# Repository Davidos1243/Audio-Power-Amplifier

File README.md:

# High-Fidelity Audio Power Amplifier (Class AB)

## 📌 Project Overview
This project involves the complete design, simulation, and PCB layout of a **Class AB audio power amplifier** designed specifically for high-frequency speakers (tweeters). The system is built around the Texas Instruments **LM3886** power amplifier IC and features active filtering using the **OPA2134** SoundPlus™ audio operational amplifiers.

### Key Features:
- **Output Power:** 60 W into an 8 Ω load.
- **Amplifier Class:** Class AB.
- **Active Crossover (Filters):**
  - High-Pass Filter (HPF) cutoff frequency: ~400 Hz.
  - Low-Pass Filter (LPF) cutoff frequency: ~20 kHz.
- **Input:** Standard 3.5mm audio jack (PC/Laptop sound card level).
- **Volume Control:** Integrated variable gain stage in the preamplifier.
- **Protection:** Built-in overvoltage, undervoltage, and SPiKe thermal protection (via LM3886).

---

## 📐 Design & Specifications

### Power Calculations
To achieve the target 60 W continuous output power for an 8 Ω speaker:
- Target speaker current: `I_rms ≈ 2.74 A`
- Target speaker voltage: `V_rms ≈ 21.91 V`
- Voltage gain required (for a 1 V input): `G ≈ 21.9 V/V`
- Power Supply: Symmetrical **±35 V** DC.
- Calculated maximum output power: `P_out ≈ 72 W` (providing safe headroom for the 60 W requirement).

### Component Selection
1. **Power Stage (LM3886):** Chosen for its high continuous average output power (up to 68 W), ultra-low distortion (0.03% THD+N), and robust SPiKe protection circuitry.
2. **Pre-amp & Active Filters (OPA2134):** Selected for its true FET-input, extremely low distortion (0.00008%), and excellent dynamic behavior tailored for high-end audio applications.

---

## 💻 LTspice Simulation
Before moving to physical design, the entire circuit was simulated in LTspice to verify stability, frequency response, and power efficiency.

### 1. Frequency Filters (Bode Analysis)
- **High-Pass Filter (Sallen-Key):** 2nd-order active filter. Simulated cutoff frequency (`f_c`) ≈ **399.6 Hz** with a stopband roll-off of -40 dB/decade.
- **Low-Pass Filter:** 2nd-order active filter. Simulated cutoff frequency (`f_c`) ≈ **20.8 kHz** with a stopband roll-off of -40 dB/decade.

### 2. Transient & Power Analysis
- Simulated using a 1 kHz sine wave input.
- Input voltage: `1 V` | Output voltage: `~32 V` (peak).
- Verified the required 60 W average power on the 8 Ω load.
- **Calculated Efficiency:** `η ≈ 71%` (at maximum power output).

---

## 🖨️ PCB Design (KiCAD)
The schematic was transferred to KiCAD for PCB layout. The physical layout was designed with strict analog audio guidelines:
- **Signal Flow:** Left-to-right signal path to prevent interference.
- **Trace Widths:** Calculated and adjusted for high-current power and output lines.
- **Grounding:** Large copper ground planes implemented to minimize noise and improve shielding.
- **Thermal Management:** Dedicated space and mounting holes provided for the LM3886 heatsink.
- **I/O:** Strategic placement of the 3.5mm jack, power terminals, and output connectors at the board edges.
- Form Factor: 2-layer FR-4 board, 50.8 x 48.26 mm.

---

## 🛠️ Bill of Materials (BOM)
Key components used in this design (SMD 0805 for passives to maintain a compact footprint):
- **ICs:** 1x LM3886, 2x OPA2134
- **Capacitors (SMD):** 1 nF, 2.2 nF, 100 nF, 120 nF, 220 nF, 1 µF
- **Resistors (SMD):** 100 Ω, 366.9 Ω, 500 Ω, 1.8 kΩ, 2 kΩ, 3.9 kΩ, 6.8 kΩ
- **Connectors:** 3.5mm Audio Jack, Molex SL Screw Terminals
- **Controls:** 10 kΩ THT Potentiometer for volume control

## 📦 Manufacturing
The PCB was cost-analyzed and prepared for fabrication using **JLCPCB** specifications:
- **Material:** FR4-TG135 (1.6mm thickness)
- **Copper Weight:** 1 oz
- **Surface Finish:** HASL

---

## 👨‍💻 Author
**Davyd Tkalich**  
*Electrical and Computer Engineering | Hardware Design Enthusiast*  
[LinkedIn](https://linkedin.com/in/davyd-tkalich-41916b277) | Edmonton, AB, Canada

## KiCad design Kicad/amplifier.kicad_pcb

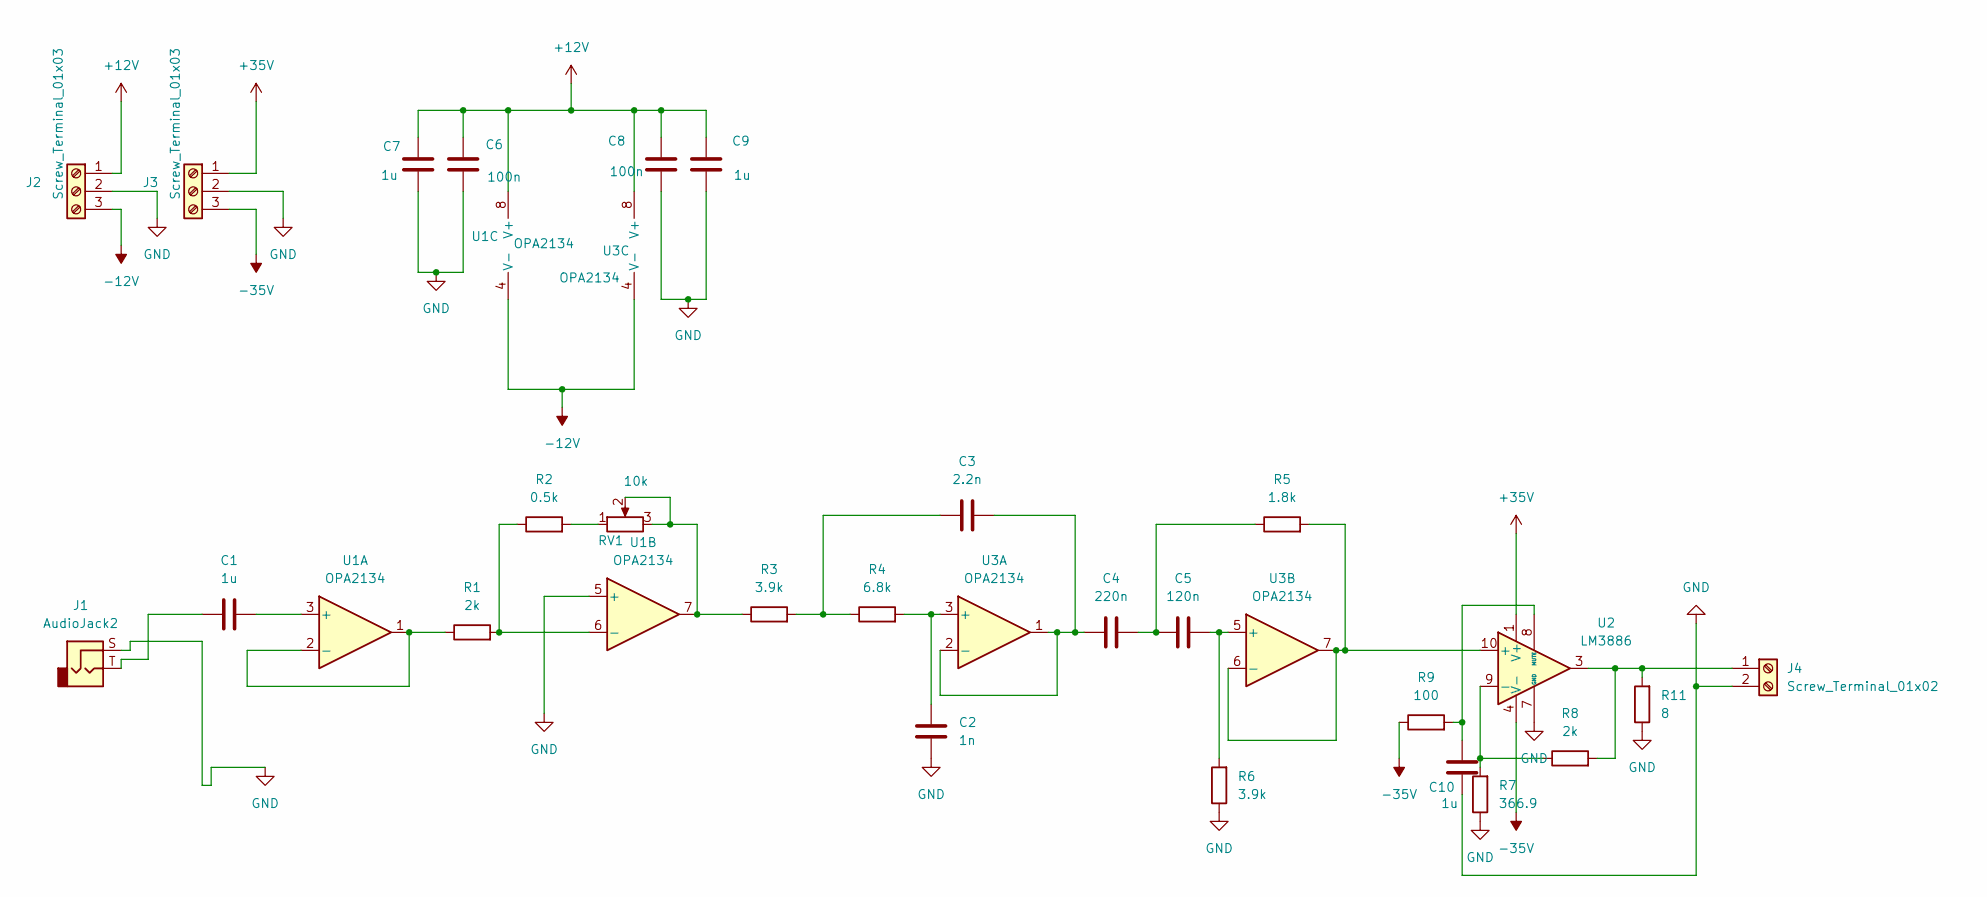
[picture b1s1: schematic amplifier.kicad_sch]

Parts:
C1, C7, C9, C10: 1u; C_0805_2012Metric
C2: 1n; C_0805_2012Metric
C3: 2.2n; C_0805_2012Metric
C4: 220n; C_0805_2012Metric
C5: 120n; C_0805_2012Metric
C6, C8: 100n; C_0805_2012Metric
J1: AudioJack2; Jack_3.5mm_CUI_SJ1-3533NG_Horizontal
J2, J3: Screw_Terminal_01x03; Molex_SL_171971-0003_1x03_P2.54mm_Vertical
J4: Screw_Terminal_01x02; Molex_SL_171971-0002_1x02_P2.54mm_Vertical
R1, R8: 2k; R_0805_2012Metric_Pad1.20x1.40mm_HandSolder
R2: 0.5k; R_0805_2012Metric_Pad1.20x1.40mm_HandSolder
R3, R6: 3.9k; R_0805_2012Metric_Pad1.20x1.40mm_HandSolder
R4: 6.8k; R_0805_2012Metric_Pad1.20x1.40mm_HandSolder
R5: 1.8k; R_0805_2012Metric_Pad1.20x1.40mm_HandSolder
R7: 366.9; R_0805_2012Metric_Pad1.20x1.40mm_HandSolder
R9: 100; R_0805_2012Metric_Pad1.20x1.40mm_HandSolder
R11: 8; R_0805_2012Metric_Pad1.20x1.40mm_HandSolder
RV1: 10k; Potentiometer_ACP_CA14-H4_Horizontal
U1, U3: OPA2134; SOIC-8-1EP_3.9x4.9mm_P1.27mm_EP2.29x3mm
U2: LM3886; TO-220F-11_P3.4x5.08mm_StaggerOdd_Lead5.08mm_Vertical

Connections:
+12V: C6.1, C7.1, C8.1, C9.1, J2.1, U1.8 (V+), U3.8 (V+)
+35V: J3.1, U2.1 (V+), U2.5 (V+)
-12V: J2.3, U1.4 (V-), U3.4 (V-)
-35V: J3.3, R9.1, U2.4 (V-)
GND: C2.2, C6.2, C7.2, C8.2, C9.2, C10.2, J1.S, J2.2, J3.2, J4.2, R6.1, R7.1, R11.1, U1.5 (+), U2.7 (GND)
unnamed: C1.1, J1.T
unnamed: C3.2, R3.2, R4.1
unnamed: C4.1, C5.2, R5.1
unnamed: J4.1, R8.2, R11.2, U2.3
unnamed: R2.2, RV1.1
unnamed: R3.1, RV1.2, RV1.3, U1.7
unnamed: C1.2, U1.3 (+)
unnamed: R1.1, U1.1, U1.2 (-)
unnamed: R1.2, R2.1, U1.6 (-)
unnamed: R5.2, U2.10 (+), U3.6 (-), U3.7
unnamed: R7.2, R8.1, U2.9 (-)
unnamed: C10.1, R9.2, U2.8 (MUTE)
unnamed: C2.1, R4.2, U3.3 (+)
unnamed: C3.1, C4.2, U3.1, U3.2 (-)
unnamed: C5.1, R6.2, U3.5 (+)

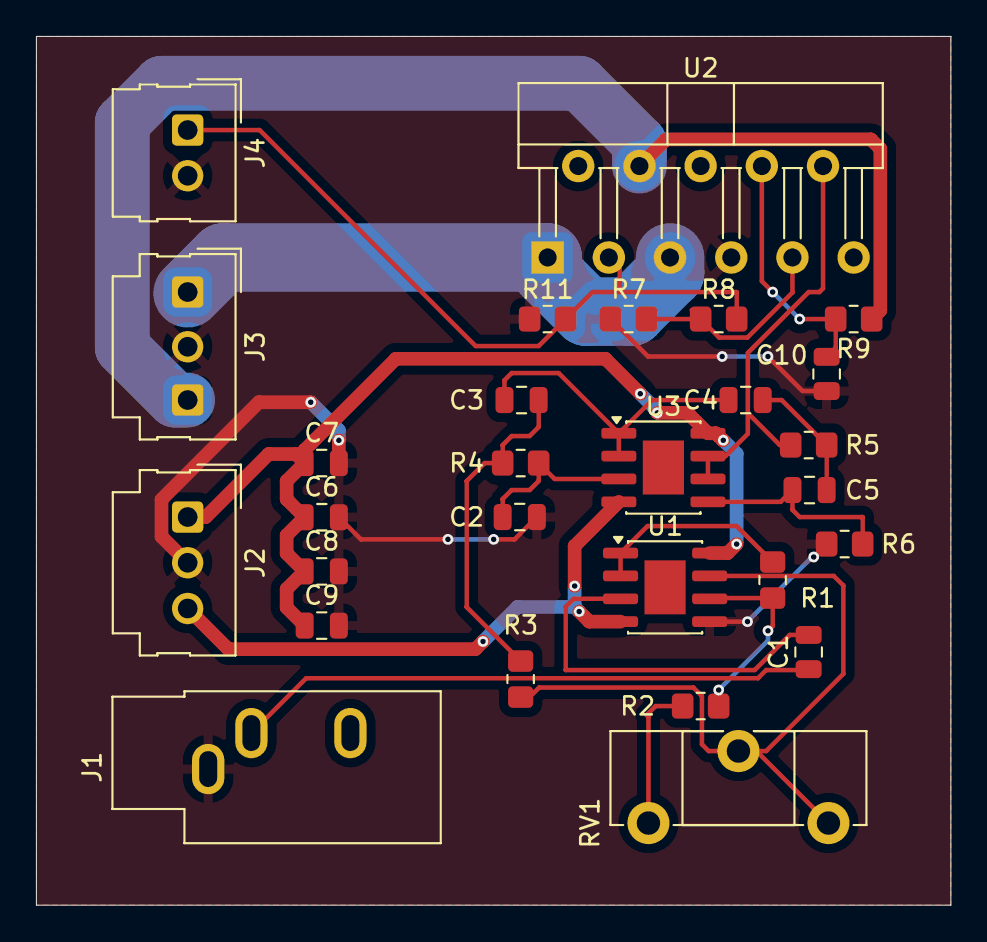
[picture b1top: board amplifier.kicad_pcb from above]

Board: 2 copper layers, 50.8 x 48.3 mm, 28 parts (0 on the bottom side), 20 nets.

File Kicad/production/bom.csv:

Designator,Footprint,Quantity,Value,LCSC Part #
"C1, C10, C7, C9",0805,4,1u,
C2,0805,1,1n,
C3,0805,1,2.2n,
C4,0805,1,220n,
C5,0805,1,120n,
"C6, C8",0805,2,100n,
J1,Jack_3.5mm_CUI_SJ1-3533NG_Horizontal,1,AudioJack2,
"J2, J3",Molex_SL_171971-0003_1x03_P2.54mm_Vertical,2,Screw_Terminal_01x03,
J4,Molex_SL_171971-0002_1x02_P2.54mm_Vertical,1,Screw_Terminal_01x02,
"R1, R8",0805,2,2k,
R11,0805,1,8,
R2,0805,1,0.5k,
"R3, R6",0805,2,3.9k,
R4,0805,1,6.8k,
R5,0805,1,1.8k,
R7,0805,1,366.9,
R9,0805,1,100,
RV1,Potentiometer_ACP_CA14-H4_Horizontal,1,10k,
"U1, U3",SOIC-8-1EP_3.9x4.9mm_P1.27mm_EP2.29x3mm,2,OPA2134,
U2,TO-220F-11_P3.4x5.08mm_StaggerOdd_Lead5.08mm_Vertical,1,LM3886,

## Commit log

2026-03-17 Revise README for High-Fidelity Audio Power Amplifier
    Updated project title and enhanced project overview with detailed specifications, design, simulation, and manufacturing information for a high-fidelity audio power amplifier.
2026-03-17 Initial commit of all project files
